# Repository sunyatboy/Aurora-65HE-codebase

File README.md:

# Aurora-65HE-codebase
Aurora 65 HE Keyboard created for Fallen in Hack Club. What makes this keyboard special is that the actuation points will change based on your typing habits. For example, if I was typing, "typing", and I accidentally typed "typinf", the actuation point of F would be much lower while G would be higher. 
## Toolchain
gcc.exe (Rev4, Built by MSYS2 project) 16.2.0
GNU gdb (GDB) 18.1
GNU Make 4.4.1

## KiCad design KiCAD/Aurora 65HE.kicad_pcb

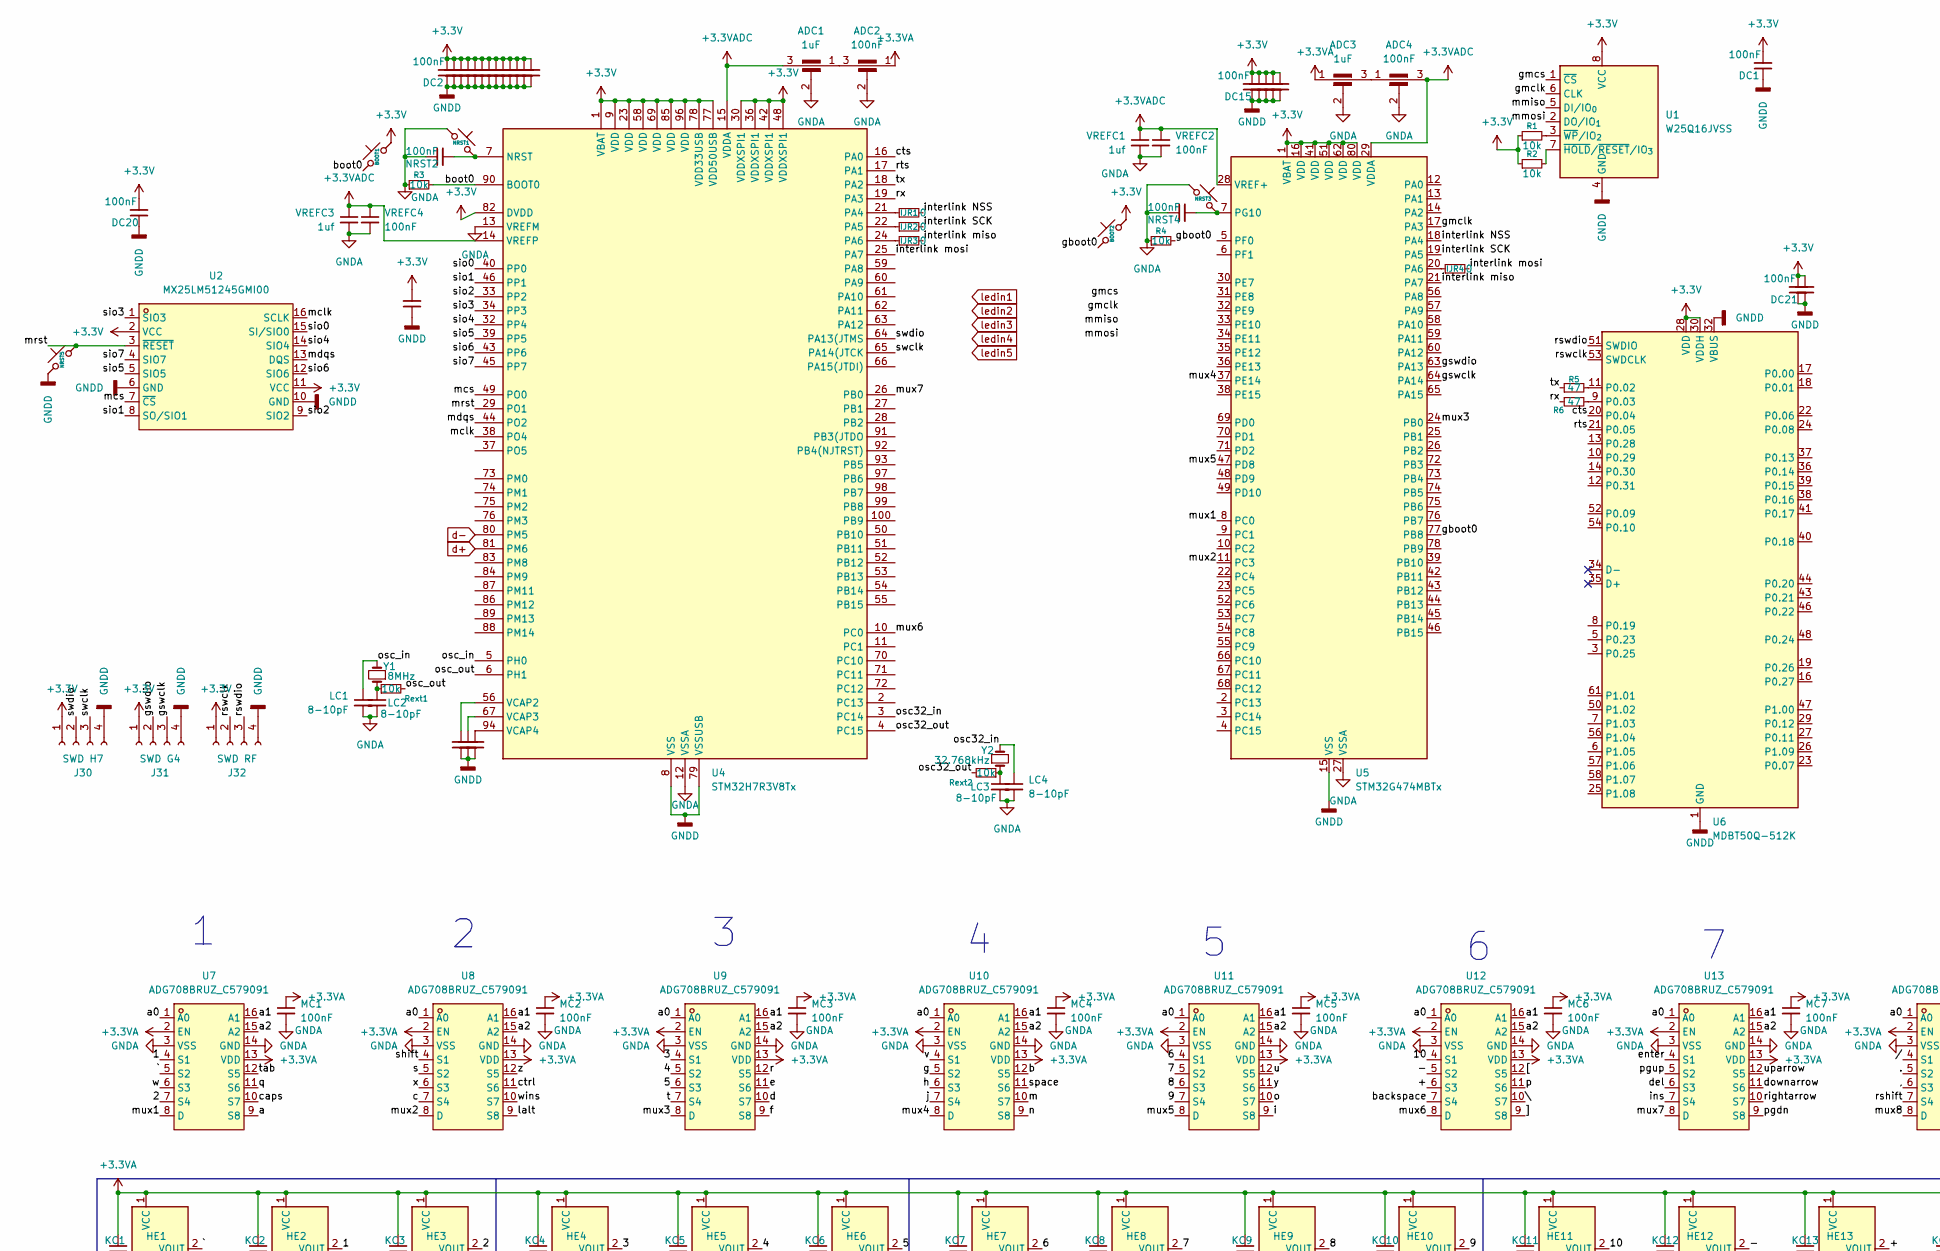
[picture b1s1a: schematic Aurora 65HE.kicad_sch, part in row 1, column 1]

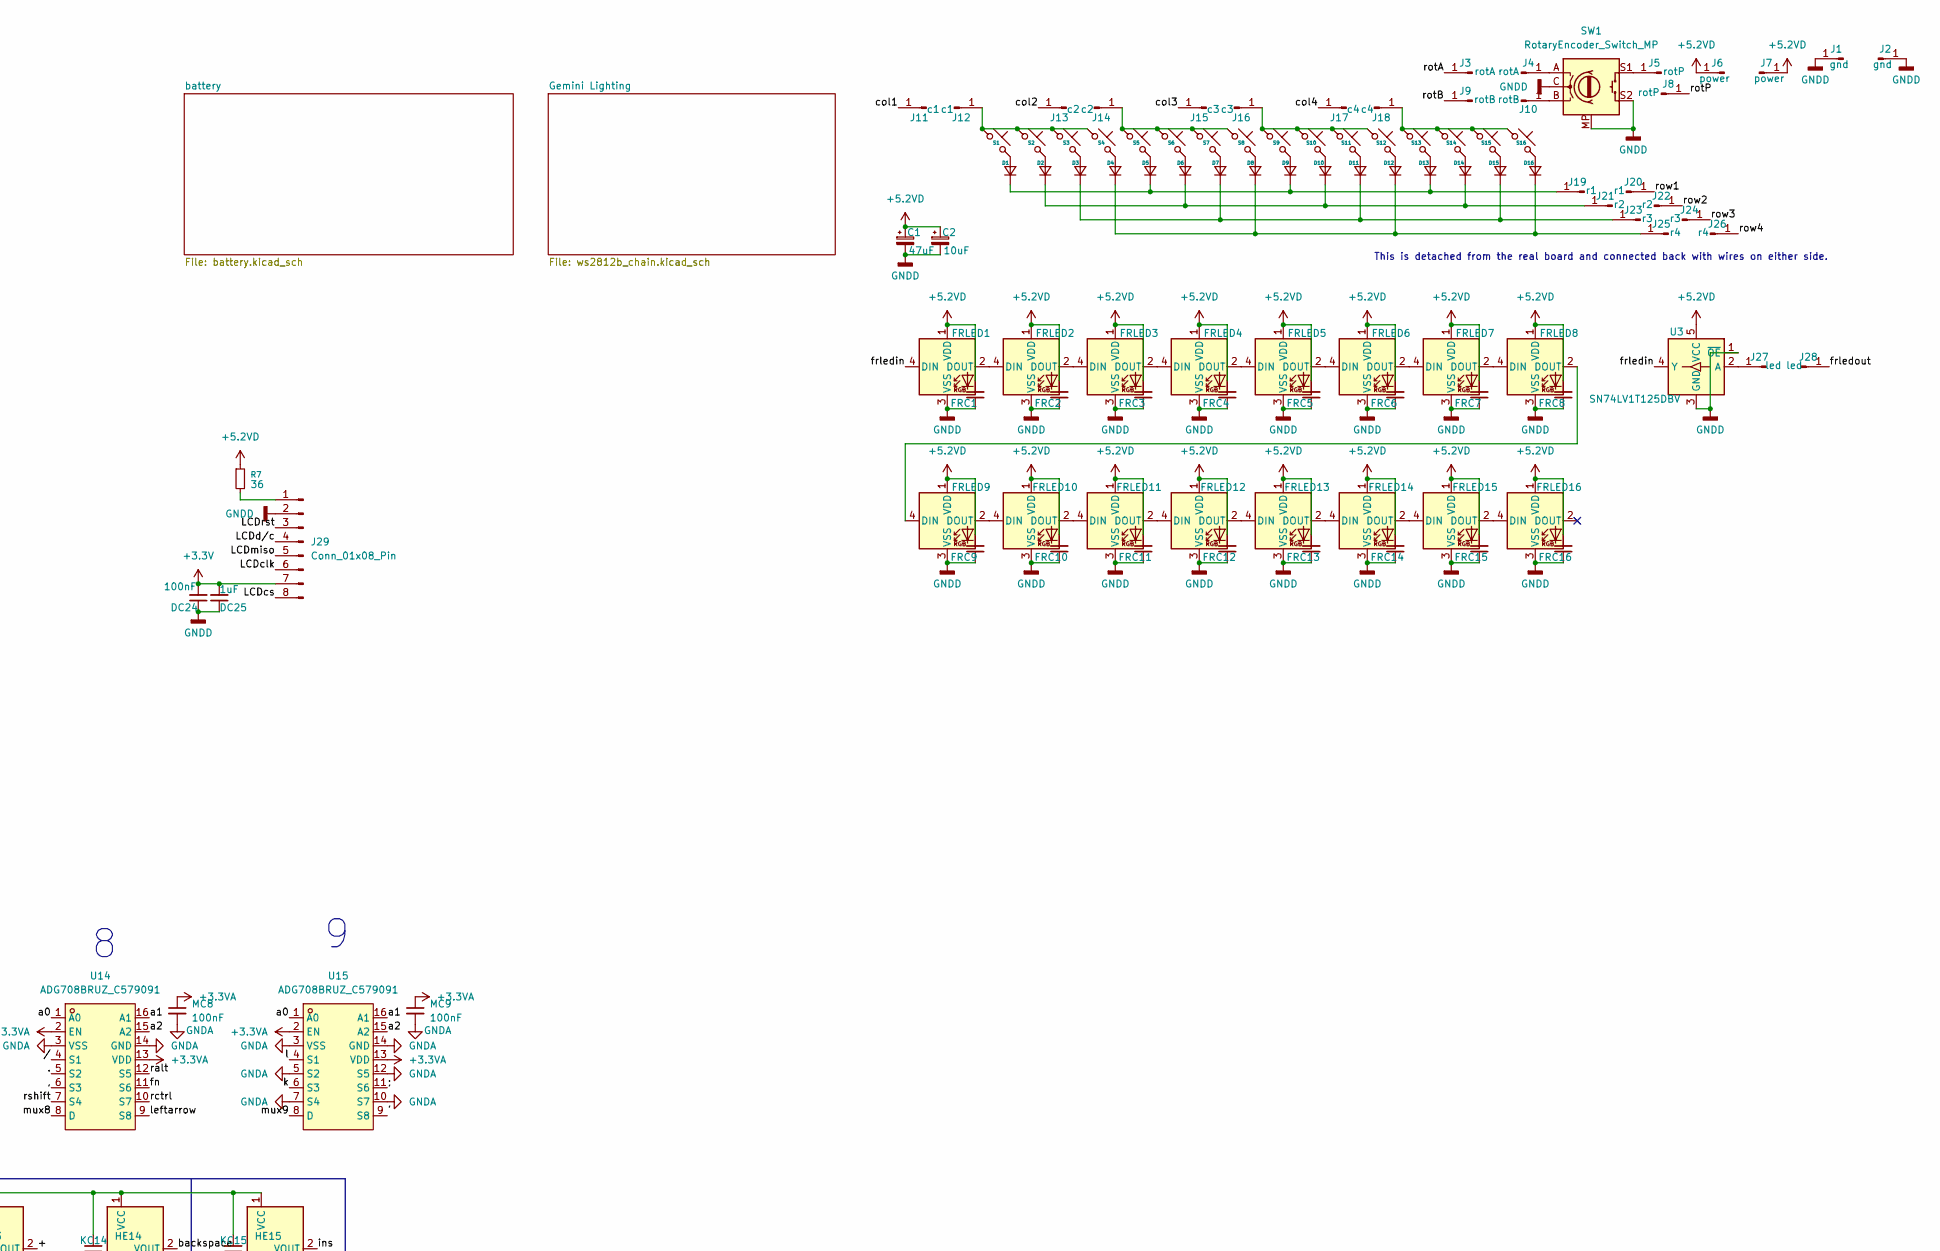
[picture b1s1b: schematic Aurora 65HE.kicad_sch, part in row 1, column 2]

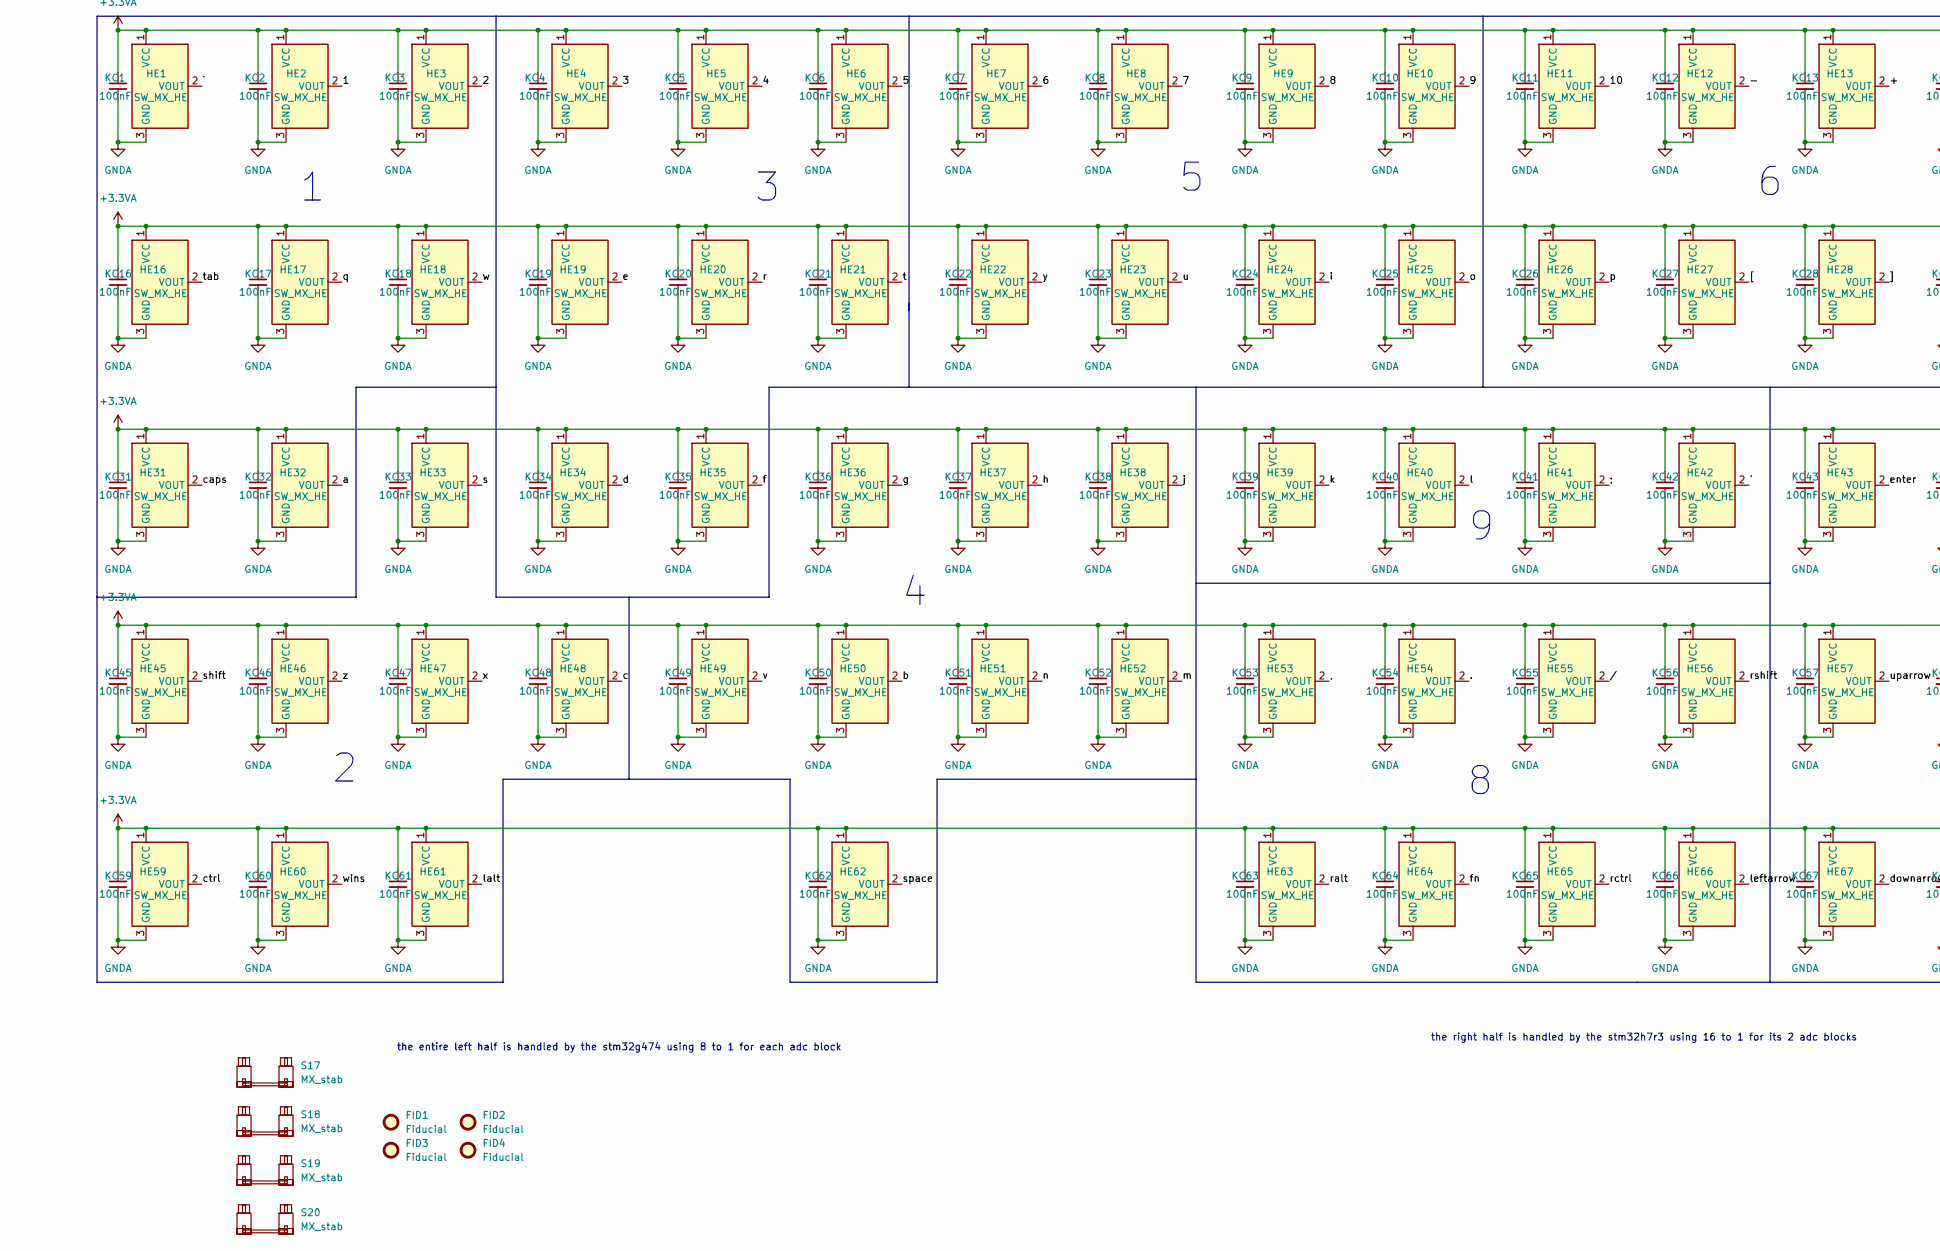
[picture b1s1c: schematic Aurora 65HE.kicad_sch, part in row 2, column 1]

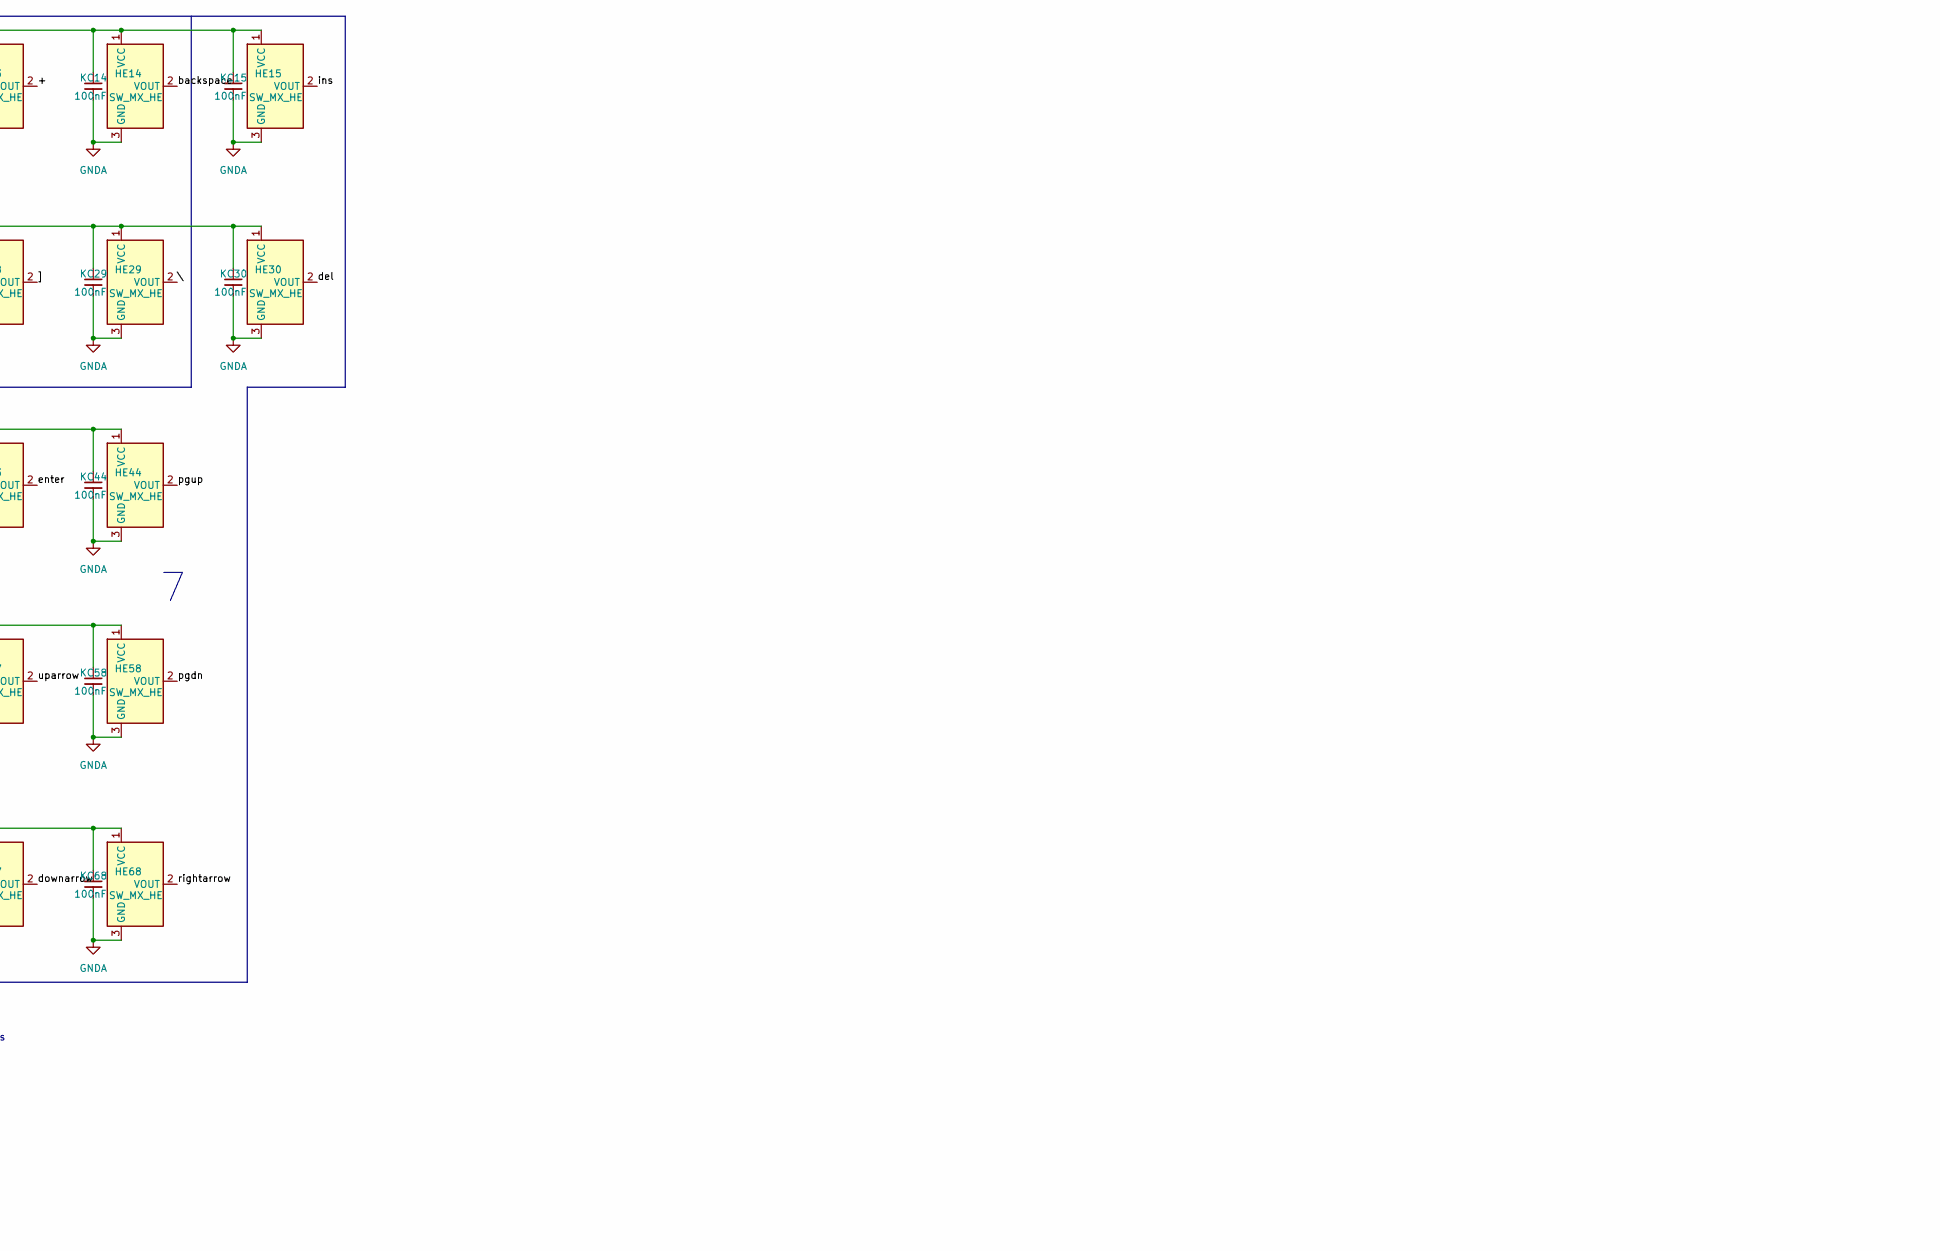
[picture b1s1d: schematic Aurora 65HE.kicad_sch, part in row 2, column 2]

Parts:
ADC1, ADC3: 1uF; FILTER-SMD_4P-L2.0-W1.3_NFM21HC105R1C3D
ADC2, ADC4: 100nF; FILTER-SMD_4P-L2.0-W1.3_NFM21HC105R1C3D
BOOT1, BOOT2: SW-TH_4P-L6.0-W6.0-P4.50-LS6.5
C1: 47uF; C_1210_3225Metric_Pad1.33x2.70mm_HandSolder
C2: 10uF; C_1210_3225Metric_Pad1.33x2.70mm_HandSolder
D1, D2, D3, D4, D5, D6, D7, D8, D9, D10, D11, D12, D13, D14, D15, D16: D_SOD-123
DC1, DC2, DC3, DC4, DC5, DC6, DC7, DC8, DC9, DC10, DC11, DC12, DC13, DC14, DC15, DC16, DC17, DC18, DC19, DC20, DC21, DC22, DC23, DC24, DC26, DC27, DC28: 100nF; C_0805_2012Metric_Pad1.18x1.45mm_HandSolder
DC25: 1uF; C_0805_2012Metric_Pad1.18x1.45mm_HandSolder
FID1, FID2, FID3, FID4: Fiducial; Fiducial_1mm_Mask2mm
FRC1, FRC2, FRC3, FRC4, FRC5, FRC6, FRC7, FRC8, FRC9, FRC10, FRC11, FRC12, FRC13, FRC14, FRC15, FRC16: 100nF; C_0805_2012Metric_Pad1.18x1.45mm_HandSolder
FRLED1, FRLED2, FRLED3, FRLED4, FRLED5, FRLED6, FRLED7, FRLED8, FRLED9, FRLED10, FRLED11, FRLED12, FRLED13, FRLED14, FRLED15, FRLED16: WS2812B; LED_WS2812B_PLCC4_5.0x5.0mm_P3.2mm
HE1, HE2, HE3, HE4, HE5, HE6, HE7, HE8, HE9, HE10, HE11, HE12, HE13, HE14, HE15, HE16, HE17, HE18, HE19, HE20, HE21, HE22, HE23, HE24, HE25, HE26, HE27, HE28, HE29, HE30, HE31, HE32, HE33, HE34, HE35, HE36, HE37, HE38, HE39, HE40, HE41, HE42, HE43, HE44, HE45, HE46, HE47, HE48, HE49, HE50, HE51, HE52, HE53, HE54, HE55, HE56, HE57, HE58, HE59, HE60, HE61, HE62, HE63, HE64, HE65, HE66, HE67, HE68: SW_MX_HE; SW_MX_HE_0deg_1u
IJR1, IJR2, IJR3, IJR4: 0; R_1206_3216Metric_Pad1.30x1.75mm_HandSolder
J1, J2: gnd; TestPoint_Plated_Hole_D2.0mm
J3, J4: rotA; TestPoint_Plated_Hole_D2.0mm
J5, J8: rotP; TestPoint_Plated_Hole_D2.0mm
J6, J7: power; TestPoint_Plated_Hole_D2.0mm
J9, J10: rotB; TestPoint_Plated_Hole_D2.0mm
J11, J12: c1; TestPoint_Plated_Hole_D2.0mm
J13, J14: c2; TestPoint_Plated_Hole_D2.0mm
J15, J16: c3; TestPoint_Plated_Hole_D2.0mm
J17, J18: c4; TestPoint_Plated_Hole_D2.0mm
J19, J20: r1; TestPoint_Plated_Hole_D2.0mm
J21, J22: r2; TestPoint_Plated_Hole_D2.0mm
J23, J24: r3; TestPoint_Plated_Hole_D2.0mm
J25, J26: r4; TestPoint_Plated_Hole_D2.0mm
J27, J28: led; TestPoint_Plated_Hole_D2.0mm
J29: Conn_01x08_Pin
J30: SWD H7; PinSocket_1x04_P1.00mm_Vertical
J31: SWD G4; PinSocket_1x04_P1.00mm_Vertical
J32: SWD RF; PinSocket_1x04_P1.00mm_Vertical
KC1, KC2, KC3, KC4, KC5, KC6, KC7, KC8, KC9, KC10, KC11, KC12, KC13, KC14, KC15, KC16, KC17, KC18, KC19, KC20, KC21, KC22, KC23, KC24, KC25, KC26, KC27, KC28, KC29, KC30, KC31, KC32, KC33, KC34, KC35, KC36, KC37, KC38, KC39, KC40, KC41, KC42, KC43, KC44, KC45, KC46, KC47, KC48, KC49, KC50, KC51, KC52, KC53, KC54, KC55, KC56, KC57, KC58, KC59, KC60, KC61, KC62, KC63, KC64, KC65, KC66, KC67, KC68: 100nF; C_0805_2012Metric_Pad1.18x1.45mm_HandSolder
LC1, LC2, LC3, LC4: 8-10pF; C_0805_2012Metric_Pad1.18x1.45mm_HandSolder
MC1, MC2, MC3, MC4, MC5, MC6, MC7, MC8, MC9: 100nF; C_0805_2012Metric_Pad1.18x1.45mm_HandSolder
NRST1, NRST3, NRST5: SW-TH_4P-L6.0-W6.0-P4.50-LS6.5
NRST2, NRST4: 100nF; C_0805_2012Metric_Pad1.18x1.45mm_HandSolder
R1, R2, R3, R4: 10k; R_0805_2012Metric_Pad1.20x1.40mm_HandSolder
R5, R6: 47; R_0805_2012Metric_Pad1.20x1.40mm_HandSolder
R7: 36; R_1210_3225Metric_Pad1.30x2.65mm_HandSolder
Rext1, Rext2: 10k; R_0805_2012Metric_Pad1.20x1.40mm_HandSolder
S1, S2, S3, S4, S5, S6, S7, S8, S9, S10, S11, S12, S13, S14, S15, S16: MX-Hotswap-1U
S17: MX_stab; STAB_MX_2u
S18, S19: MX_stab; STAB_MX_2.25u
S20: MX_stab; STAB_MX_6.25u
SW1: RotaryEncoder_Switch_MP; ROT_Alps_EC11E-Switch
U1: W25Q16JVSS; SOIC-8_5.3x5.3mm_P1.27mm
U2: MX25LM51245GMI00; SO-16_L10.3-W7.5-P1.27-LS10.3-BL; MPN MX25LM51245GMI00; LCSC Part C7425126
U3: SN74LV1T125DBV; SOT-23-5
U4: STM32H7R3V8Tx; LQFP-100_14x14mm_P0.5mm
U5: STM32G474MBTx; LQFP-80_12x12mm_P0.5mm
U6: MDBT50Q-512K; Raytac_MDBT50Q
U7, U8, U9, U10, U11, U12, U13, U14, U15: ADG708BRUZ_C579091; TSSOP-16_L5.0-W4.4-P0.65-LS6.4-BL; MPN ADG708BRUZ; LCSC Part C579091
VREFC1, VREFC3: 1uf
VREFC2, VREFC4: 100nF
Y1: 8MHz; OSC-TH_BD2.0-P0.70-D0.3
Y2: 32.768kHz; OSC-TH_BD2.0-P0.70-D0.3

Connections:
+3.3V: BOOT1.2, BOOT2.2, DC1.2, DC2.2, DC3.2, DC4.2, DC5.2, DC6.2, DC7.2, DC8.2, DC9.2, DC10.2, DC11.2, DC12.2, DC13.2, DC14.2, DC15.2, DC16.2, DC17.2, DC18.2, DC19.2, DC20.2, DC21.2, DC22.2, DC23.2, DC24.2, DC25.2, J29.7, J30.1, J31.1, J32.1, R1.1, R2.1, U1.8 (VCC), U2.2 (VCC), U2.11 (VCC), U4.1 (VBAT), U4.9 (VDD), U4.23 (VDD), U4.30 (VDDXSPI1), U4.36 (VDDXSPI1), U4.42 (VDDXSPI1), U4.48 (VDDXSPI1), U4.58 (VDD), U4.69 (VDD), U4.77 (VDD50USB), U4.78 (VDD33USB), U4.82 (DVDD), U4.85 (VDD), U4.96 (VDD), U5.1 (VBAT), U5.16 (VDD), U5.41 (VDD), U5.51 (VDD), U5.62 (VDD), U5.80 (VDD), U6.28 (VDD), U6.30 (VDDH); also elsewhere on the board
+3.3VA: ADC2.1, ADC3.1, HE1.1 (VCC), HE2.1 (VCC), HE3.1 (VCC), HE4.1 (VCC), HE5.1 (VCC), HE6.1 (VCC), HE7.1 (VCC), HE8.1 (VCC), HE9.1 (VCC), HE10.1 (VCC), HE11.1 (VCC), HE12.1 (VCC), HE13.1 (VCC), HE14.1 (VCC), HE15.1 (VCC), HE16.1 (VCC), HE17.1 (VCC), HE18.1 (VCC), HE19.1 (VCC), HE20.1 (VCC), HE21.1 (VCC), HE22.1 (VCC), HE23.1 (VCC), HE24.1 (VCC), HE25.1 (VCC), HE26.1 (VCC), HE27.1 (VCC), HE28.1 (VCC), HE29.1 (VCC), HE30.1 (VCC), HE31.1 (VCC), HE32.1 (VCC), HE33.1 (VCC), HE34.1 (VCC), HE35.1 (VCC), HE36.1 (VCC), HE37.1 (VCC), HE38.1 (VCC), HE39.1 (VCC), HE40.1 (VCC), HE41.1 (VCC), HE42.1 (VCC), HE43.1 (VCC), HE44.1 (VCC), HE45.1 (VCC), HE46.1 (VCC), HE47.1 (VCC), HE48.1 (VCC), HE49.1 (VCC), HE50.1 (VCC), HE51.1 (VCC), HE52.1 (VCC), HE53.1 (VCC), HE54.1 (VCC), HE55.1 (VCC), HE56.1 (VCC), HE57.1 (VCC), HE58.1 (VCC), HE59.1 (VCC), HE60.1 (VCC), HE61.1 (VCC), HE62.1 (VCC), HE63.1 (VCC), HE64.1 (VCC), HE65.1 (VCC), HE66.1 (VCC), HE67.1 (VCC), HE68.1 (VCC), KC1.1, KC2.1, KC3.1, KC4.1, KC5.1, KC6.1, KC7.1, KC8.1, KC9.1, KC10.1, KC11.1, KC12.1, KC13.1, KC14.1, KC15.1, KC16.1, KC17.1, KC18.1, KC19.1, KC20.1, KC21.1, KC22.1, KC23.1, KC24.1, KC25.1, KC26.1, KC27.1, KC28.1, KC29.1, KC30.1, KC31.1, KC32.1, KC33.1, KC34.1, KC35.1, KC36.1, KC37.1, KC38.1, KC39.1, KC40.1, KC41.1, KC42.1, KC43.1, KC44.1, KC45.1, KC46.1, KC47.1, KC48.1, KC49.1, KC50.1, KC51.1, KC52.1, KC53.1, KC54.1, KC55.1, KC56.1, KC57.1, KC58.1, KC59.1, KC60.1, KC61.1, KC62.1, KC63.1, KC64.1, KC65.1, KC66.1, KC67.1, KC68.1, MC1.1, MC2.1, MC3.1, MC4.1, MC5.1, MC6.1, MC7.1, MC8.1, MC9.1, U7.2 (EN), U7.13 (VDD), U8.2 (EN), U8.13 (VDD), U9.2 (EN), U9.13 (VDD), U10.2 (EN), U10.13 (VDD), U11.2 (EN), U11.13 (VDD), U12.2 (EN), U12.13 (VDD), U13.2 (EN), U13.13 (VDD), U14.2 (EN), U14.13 (VDD), U15.2 (EN), U15.13 (VDD); also elsewhere on the board
+3.3VADC: ADC1.3, ADC4.3, U4.14 (VREFP), U4.15 (VDDA), U5.28 (VREF+), U5.29 (VDDA), VREFC1.1, VREFC2.1, VREFC3.1, VREFC4.1
+5.2VD: C1.1, C2.1, FRC1.2, FRC2.2, FRC3.2, FRC4.2, FRC5.2, FRC6.2, FRC7.2, FRC8.2, FRC9.2, FRC10.2, FRC11.2, FRC12.2, FRC13.2, FRC14.2, FRC15.2, FRC16.2, FRLED1.1 (VDD), FRLED2.1 (VDD), FRLED3.1 (VDD), FRLED4.1 (VDD), FRLED5.1 (VDD), FRLED6.1 (VDD), FRLED7.1 (VDD), FRLED8.1 (VDD), FRLED9.1 (VDD), FRLED10.1 (VDD), FRLED11.1 (VDD), FRLED12.1 (VDD), FRLED13.1 (VDD), FRLED14.1 (VDD), FRLED15.1 (VDD), FRLED16.1 (VDD), J6.1 (Pin_1_1), J7.1 (Pin_1_1), R7.1, U3.5 (VCC); also elsewhere on the board
/1: HE2.2 (VOUT), U7.4 (S1)
/2: HE3.2 (VOUT), U7.7 (S4)
/3: HE4.2 (VOUT), U9.4 (S1)
/4: HE5.2 (VOUT), U9.5 (S2)
/5: HE6.2 (VOUT), U9.6 (S3)
/6: HE7.2 (VOUT), U11.4 (S1)
/7: HE8.2 (VOUT), U11.5 (S2)
/8: HE9.2 (VOUT), U11.6 (S3)
/9: HE10.2 (VOUT), U11.7 (S4)
/10: HE11.2 (VOUT), U12.4 (S1)
/': HE42.2 (VOUT), U15.9 (S8)
/+: HE13.2 (VOUT), U12.6 (S3)
/,: HE53.2 (VOUT), U14.6 (S3)
/-: HE12.2 (VOUT), U12.5 (S2)
/.: HE54.2 (VOUT), U14.5 (S2)
/;: HE41.2 (VOUT), U15.11 (S6)
/[: HE27.2 (VOUT), U12.12 (S5)
/\: HE29.2 (VOUT), U12.10 (S7)
/]: HE28.2 (VOUT), U12.9 (S8)
/`: HE1.2 (VOUT), U7.5 (S2)
/a: HE32.2 (VOUT), U7.9 (S8)
/a0: U7.1 (A0), U8.1 (A0), U9.1 (A0), U10.1 (A0), U11.1 (A0), U12.1 (A0), U13.1 (A0), U14.1 (A0), U15.1 (A0)
/a1: U7.16 (A1), U8.16 (A1), U9.16 (A1), U10.16 (A1), U11.16 (A1), U12.16 (A1), U13.16 (A1), U14.16 (A1), U15.16 (A1)
/a2: U7.15 (A2), U8.15 (A2), U9.15 (A2), U10.15 (A2), U11.15 (A2), U12.15 (A2), U13.15 (A2), U14.15 (A2), U15.15 (A2)
/b: HE50.2 (VOUT), U10.12 (S5)
/backspace: HE14.2 (VOUT), U12.7 (S4)
/boot0: BOOT1.1, R3.2, U4.90 (BOOT0)
/c: HE48.2 (VOUT), U8.7 (S4)
/caps: HE31.2 (VOUT), U7.10 (S7)
/col1: J11.1 (Pin_1_1)
/col2: J13.1 (Pin_1_1)
/col3: J15.1 (Pin_1_1)
/col4: J17.1 (Pin_1_1)
/ctrl: HE59.2 (VOUT), U8.11 (S6)
/cts: U4.16 (PA0), U6.20 (P0.04)
/d: HE34.2 (VOUT), U9.10 (S7)
/del: HE30.2 (VOUT), U13.6 (S3)
/downarrow: HE67.2 (VOUT), U13.11 (S6)
/e: HE19.2 (VOUT), U9.11 (S6)
/enter: HE43.2 (VOUT), U13.4 (S1)
/f: HE35.2 (VOUT), U9.9 (S8)
/fn: HE64.2 (VOUT), U14.11 (S6)
/frledin: FRLED1.4 (DIN), U3.4 (Y)
/frledout: J28.1 (Pin_1_1)
/g: HE36.2 (VOUT), U10.5 (S2)
/gboot0: BOOT2.1, R4.2, U5.77 (PB8)
/gmclk: U1.6 (CLK), U5.17 (PA3)
/gmcs: U1.1 (~CS)
/gswclk: J31.3, U5.64 (PA14)
/gswdio: J31.2, U5.63 (PA13)
/h: HE37.2 (VOUT), U10.6 (S3)
/i: HE24.2 (VOUT), U11.9 (S8)
/ins: HE15.2 (VOUT), U13.7 (S4)
/interlink NSS: IJR1.2, U5.18 (PA4)
/interlink SCK: IJR2.2, U5.19 (PA5)
/interlink miso: IJR3.2, U5.21 (PA7)
/interlink mosi: IJR4.2, U4.25 (PA7)
/j: HE38.2 (VOUT), U10.7 (S4)
/k: HE39.2 (VOUT), U15.6 (S3)
/l: HE40.2 (VOUT), U15.4 (S1)
/lalt: HE61.2 (VOUT), U8.9 (S8)
/leftarrow: HE66.2 (VOUT), U14.9 (S8)
/m: HE52.2 (VOUT), U10.10 (S7)
/mclk: U2.16 (SCLK), U4.38 (PO4)
/mcs: U2.7 (~CS), U4.49 (PO0)
/mdqs: U2.13 (DQS), U4.44 (PO2)
/mmiso: U1.5 (DI/IO_{0})
/mmosi: U1.2 (DO/IO_{1})
/mrst: NRST5.2, U2.3 (~RESET), U4.29 (PO1)
/mux1: U5.8 (PC0), U7.8 (D)
/mux2: U5.11 (PC3), U8.8 (D)
/mux3: U5.24 (PB0), U9.8 (D)
/mux4: U5.37 (PE14), U10.8 (D)
/mux5: U5.47 (PD8), U11.8 (D)
/mux6: U4.10 (PC0), U12.8 (D)
/mux7: U4.26 (PB0), U13.8 (D)
/mux8: U14.8 (D)
/mux9: U15.8 (D)
/n: HE51.2 (VOUT), U10.9 (S8)
/o: HE25.2 (VOUT), U11.10 (S7)
/osc32_in: LC4.1, U4.3 (PC14), Y2.2
/osc32_out: Rext2.2, U4.4 (PC15)
/osc_in: LC1.1, U4.5 (PH0), Y1.2
/osc_out: Rext1.2, U4.6 (PH1)
/p: HE26.2 (VOUT), U12.11 (S6)
/pgdn: HE58.2 (VOUT), U13.9 (S8)
/pgup: HE44.2 (VOUT), U13.5 (S2)
/q: HE17.2 (VOUT), U7.11 (S6)
/r: HE20.2 (VOUT), U9.12 (S5)
/ralt: HE63.2 (VOUT), U14.12 (S5)
/rctrl: HE65.2 (VOUT), U14.10 (S7)
/rightarrow: HE68.2 (VOUT), U13.10 (S7)
/rotA: J3.1 (Pin_1_1)
/rotB: J9.1 (Pin_1_1)
/rotP: J8.1 (Pin_1_1)
/row1: J20.1 (Pin_1_1)
/row2: J22.1 (Pin_1_1)
/row3: J24.1 (Pin_1_1)
/row4: J26.1 (Pin_1_1)
/rshift: HE56.2 (VOUT), U14.7 (S4)
/rswclk: J32.2, U6.53 (SWDCLK)
/rswdio: J32.3, U6.51 (SWDIO)
/rts: U4.17 (PA1), U6.21 (P0.05)
/rx: R6.1, U4.19 (PA3)
/s: HE33.2 (VOUT), U8.5 (S2)
/shift: HE45.2 (VOUT), U8.4 (S1)
/sio0: U2.15 (SI/SIO0), U4.40 (PP0)
/sio1: U2.8 (SO/SIO1), U4.46 (PP1)
/sio2: U2.9 (SIO2), U4.33 (PP2)
/sio3: U2.1 (SIO3), U4.34 (PP3)
/sio4: U2.14 (SIO4), U4.32 (PP4)
/sio5: U2.5 (SIO5), U4.39 (PP5)
/sio6: U2.12 (SIO6), U4.43 (PP6)
/sio7: U2.4 (SIO7), U4.45 (PP7)
/space: HE62.2 (VOUT), U10.11 (S6)
/swclk: J30.3, U4.65 (PA14(JTCK)
/swdio: J30.2, U4.64 (PA13(JTMS)
/t: HE21.2 (VOUT), U9.7 (S4)
/tab: HE16.2 (VOUT), U7.12 (S5)
/tx: R5.1, U4.18 (PA2)
/u: HE23.2 (VOUT), U11.12 (S5)
/uparrow: HE57.2 (VOUT), U13.12 (S5)
/v: HE49.2 (VOUT), U10.4 (S1)
/w: HE18.2 (VOUT), U7.6 (S3)
/wins: HE60.2 (VOUT), U8.10 (S7)
/x: HE47.2 (VOUT), U8.6 (S3)
/y: HE22.2 (VOUT), U11.11 (S6)
/z: HE46.2 (VOUT), U8.12 (S5)
//: HE55.2 (VOUT), U14.4 (S1)
GNDA: ADC1.2, ADC2.2, ADC3.2, ADC4.2, HE1.3 (GND), HE2.3 (GND), HE3.3 (GND), HE4.3 (GND), HE5.3 (GND), HE6.3 (GND), HE7.3 (GND), HE8.3 (GND), HE9.3 (GND), HE10.3 (GND), HE11.3 (GND), HE12.3 (GND), HE13.3 (GND), HE14.3 (GND), HE15.3 (GND), HE16.3 (GND), HE17.3 (GND), HE18.3 (GND), HE19.3 (GND), HE20.3 (GND), HE21.3 (GND), HE22.3 (GND), HE23.3 (GND), HE24.3 (GND), HE25.3 (GND), HE26.3 (GND), HE27.3 (GND), HE28.3 (GND), HE29.3 (GND), HE30.3 (GND), HE31.3 (GND), HE32.3 (GND), HE33.3 (GND), HE34.3 (GND), HE35.3 (GND), HE36.3 (GND), HE37.3 (GND), HE38.3 (GND), HE39.3 (GND), HE40.3 (GND), HE41.3 (GND), HE42.3 (GND), HE43.3 (GND), HE44.3 (GND), HE45.3 (GND), HE46.3 (GND), HE47.3 (GND), HE48.3 (GND), HE49.3 (GND), HE50.3 (GND), HE51.3 (GND), HE52.3 (GND), HE53.3 (GND), HE54.3 (GND), HE55.3 (GND), HE56.3 (GND), HE57.3 (GND), HE58.3 (GND), HE59.3 (GND), HE60.3 (GND), HE61.3 (GND), HE62.3 (GND), HE63.3 (GND), HE64.3 (GND), HE65.3 (GND), HE66.3 (GND), HE67.3 (GND), HE68.3 (GND), KC1.2, KC2.2, KC3.2, KC4.2, KC5.2, KC6.2, KC7.2, KC8.2, KC9.2, KC10.2, KC11.2, KC12.2, KC13.2, KC14.2, KC15.2, KC16.2, KC17.2, KC18.2, KC19.2, KC20.2, KC21.2, KC22.2, KC23.2, KC24.2, KC25.2, KC26.2, KC27.2, KC28.2, KC29.2, KC30.2, KC31.2, KC32.2, KC33.2, KC34.2, KC35.2, KC36.2, KC37.2, KC38.2, KC39.2, KC40.2, KC41.2, KC42.2, KC43.2, KC44.2, KC45.2, KC46.2, KC47.2, KC48.2, KC49.2, KC50.2, KC51.2, KC52.2, KC53.2, KC54.2, KC55.2, KC56.2, KC57.2, KC58.2, KC59.2, KC60.2, KC61.2, KC62.2, KC63.2, KC64.2, KC65.2, KC66.2, KC67.2, KC68.2, LC1.2, LC2.2, LC3.2, LC4.2, MC1.2, MC2.2, MC3.2, MC4.2, MC5.2, MC6.2, MC7.2, MC8.2, MC9.2, NRST1.1, NRST2.1, NRST3.1, NRST4.1, R3.1, R4.1, U4.12 (VSSA), U4.13 (VREFM), U5.27 (VSSA), U7.3 (VSS), U7.14 (GND), U8.3 (VSS), U8.14 (GND), U9.3 (VSS), U9.14 (GND), U10.3 (VSS), U10.14 (GND), U11.3 (VSS), U11.14 (GND), U12.3 (VSS), U12.14 (GND), U13.3 (VSS), U13.14 (GND), U14.3 (VSS), U14.14 (GND), U15.3 (VSS), U15.5 (S2), U15.7 (S4), U15.10 (S7), U15.12 (S5), U15.14 (GND), VREFC1.2, VREFC2.2, VREFC3.2, VREFC4.2; also elsewhere on the board
GNDD: C1.2, C2.2, DC1.1, DC2.1, DC3.1, DC4.1, DC5.1, DC6.1, DC7.1, DC8.1, DC9.1, DC10.1, DC11.1, DC12.1, DC13.1, DC14.1, DC15.1, DC16.1, DC17.1, DC18.1, DC19.1, DC20.1, DC21.1, DC22.1, DC23.1, DC24.1, DC25.1, DC26.1, DC27.1, DC28.1, FRC1.1, FRC2.1, FRC3.1, FRC4.1, FRC5.1, FRC6.1, FRC7.1, FRC8.1, FRC9.1, FRC10.1, FRC11.1, FRC12.1, FRC13.1, FRC14.1, FRC15.1, FRC16.1, FRLED1.3 (VSS), FRLED2.3 (VSS), FRLED3.3 (VSS), FRLED4.3 (VSS), FRLED5.3 (VSS), FRLED6.3 (VSS), FRLED7.3 (VSS), FRLED8.3 (VSS), FRLED9.3 (VSS), FRLED10.3 (VSS), FRLED11.3 (VSS), FRLED12.3 (VSS), FRLED13.3 (VSS), FRLED14.3 (VSS), FRLED15.3 (VSS), FRLED16.3 (VSS), J1.1 (Pin_1_1), J2.1 (Pin_1_1), J29.2, J30.4, J31.4, J32.4, NRST5.1, SW1.C, SW1.MP, SW1.S2, U1.4 (GND), U2.6 (GND), U2.10 (GND), U3.1 (~OE), U3.3 (GND), U4.8 (VSS), U4.20 (VSS), U4.31 (VSS), U4.35 (VSS), U4.41 (VSS), U4.47 (VSS), U4.57 (VSS), U4.68 (VSS), U4.79 (VSSUSB), U4.95 (VSS), U5.15 (VSS), U5.40 (VSS), U5.50 (VSS), U5.61 (VSS), U5.79 (VSS), U6.1 (GND), U6.2 (GND), U6.15 (GND), U6.32 (VBUS), U6.33 (GND), U6.55 (GND); also elsewhere on the board
unnamed: ADC1.1, ADC2.3
unnamed: ADC3.3, ADC4.1
unnamed: D1.2 (A), S1.2
unnamed: D1.1 (K), D5.1 (K), D9.1 (K), D13.1 (K), J19.1 (Pin_1_1)
unnamed: D2.2 (A), S2.2
unnamed: D3.2 (A), S3.2
unnamed: D4.2 (A), S4.2
unnamed: D5.2 (A), S5.2
unnamed: D6.2 (A), S6.2
unnamed: D7.2 (A), S7.2
unnamed: D8.2 (A), S8.2
unnamed: D9.2 (A), S9.2
unnamed: D10.2 (A), S10.2
unnamed: D2.1 (K), D6.1 (K), D10.1 (K), D14.1 (K), J21.1 (Pin_1_1)
unnamed: D11.2 (A), S11.2
unnamed: D3.1 (K), D7.1 (K), D11.1 (K), D15.1 (K), J23.1 (Pin_1_1)
unnamed: D12.2 (A), S12.2
unnamed: D4.1 (K), D8.1 (K), D12.1 (K), D16.1 (K), J25.1 (Pin_1_1)
unnamed: D13.2 (A), S13.2
unnamed: D14.2 (A), S14.2
unnamed: D15.2 (A), S15.2
unnamed: D16.2 (A), S16.2
unnamed: FRLED1.2 (DOUT), FRLED2.4 (DIN)
unnamed: FRLED2.2 (DOUT), FRLED3.4 (DIN)
unnamed: FRLED3.2 (DOUT), FRLED4.4 (DIN)
unnamed: FRLED4.2 (DOUT), FRLED5.4 (DIN)
unnamed: FRLED5.2 (DOUT), FRLED6.4 (DIN)
unnamed: FRLED6.2 (DOUT), FRLED7.4 (DIN)
unnamed: FRLED7.2 (DOUT), FRLED8.4 (DIN)
unnamed: FRLED8.2 (DOUT), FRLED9.4 (DIN)
unnamed: FRLED9.2 (DOUT), FRLED10.4 (DIN)
unnamed: FRLED10.2 (DOUT), FRLED11.4 (DIN)
unnamed: FRLED11.2 (DOUT), FRLED12.4 (DIN)
unnamed: FRLED12.2 (DOUT), FRLED13.4 (DIN)
unnamed: FRLED13.2 (DOUT), FRLED14.4 (DIN)
unnamed: FRLED14.2 (DOUT), FRLED15.4 (DIN)
unnamed: FRLED15.2 (DOUT), FRLED16.4 (DIN)
unnamed: J4.1 (Pin_1_1), SW1.A
unnamed: J5.1 (Pin_1_1), SW1.S1
unnamed: J10.1 (Pin_1_1), SW1.B
unnamed: J12.1 (Pin_1_1), S1.1, S2.1, S3.1, S4.1
unnamed: J14.1 (Pin_1_1), S5.1, S6.1, S7.1, S8.1
unnamed: J16.1 (Pin_1_1), S9.1, S10.1, S11.1, S12.1
unnamed: J18.1 (Pin_1_1), S13.1, S14.1, S15.1, S16.1
unnamed: J27.1 (Pin_1_1), U3.2 (A)
unnamed: J29.1, R7.2
unnamed: LC2.1, Rext1.1, Y1.1
unnamed: LC3.1, Rext2.1, Y2.1
unnamed: R2.2, U1.7 (~HOLD/~RESET/IO_{3})
unnamed: R1.2, U1.3 (~WP/IO_{2})
unnamed: NRST1.2, NRST2.2, U4.7 (NRST)
unnamed: IJR1.1, U4.21 (PA4)
unnamed: IJR2.1, U4.22 (PA5)
unnamed: IJR3.1, U4.24 (PA6)
unnamed: DC26.2, U4.56 (VCAP2)
unnamed: DC27.2, U4.67 (VCAP3)
unnamed: DC28.2, U4.94 (VCAP4)
unnamed: IJR4.1, U5.20 (PA6)
unnamed: NRST3.2, NRST4.2, U5.7 (PG10)
unnamed: R5.2, U6.11 (P0.02)
unnamed: R6.2, U6.9 (P0.03)
d+: U4.81 (PM6); also elsewhere on the board
d-: U4.80 (PM5); also elsewhere on the board

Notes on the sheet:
the right half is handled by the stm32h7r3 using 16 to 1 for its 2 adc blocks
the entire left half is handled by the stm32g474 using 8 to 1 for each adc block
This is detached from the real board and connected back with wires on either side.
